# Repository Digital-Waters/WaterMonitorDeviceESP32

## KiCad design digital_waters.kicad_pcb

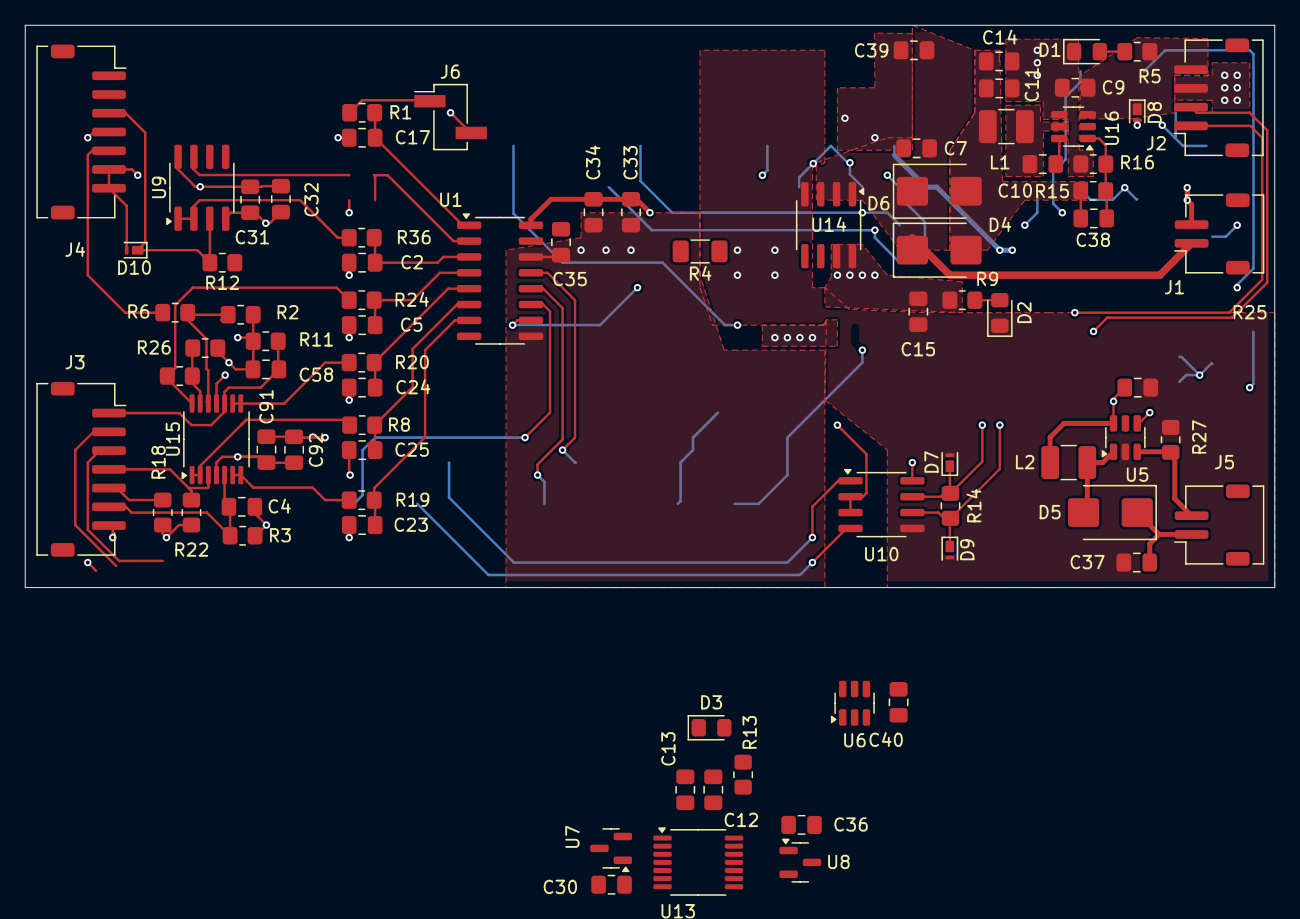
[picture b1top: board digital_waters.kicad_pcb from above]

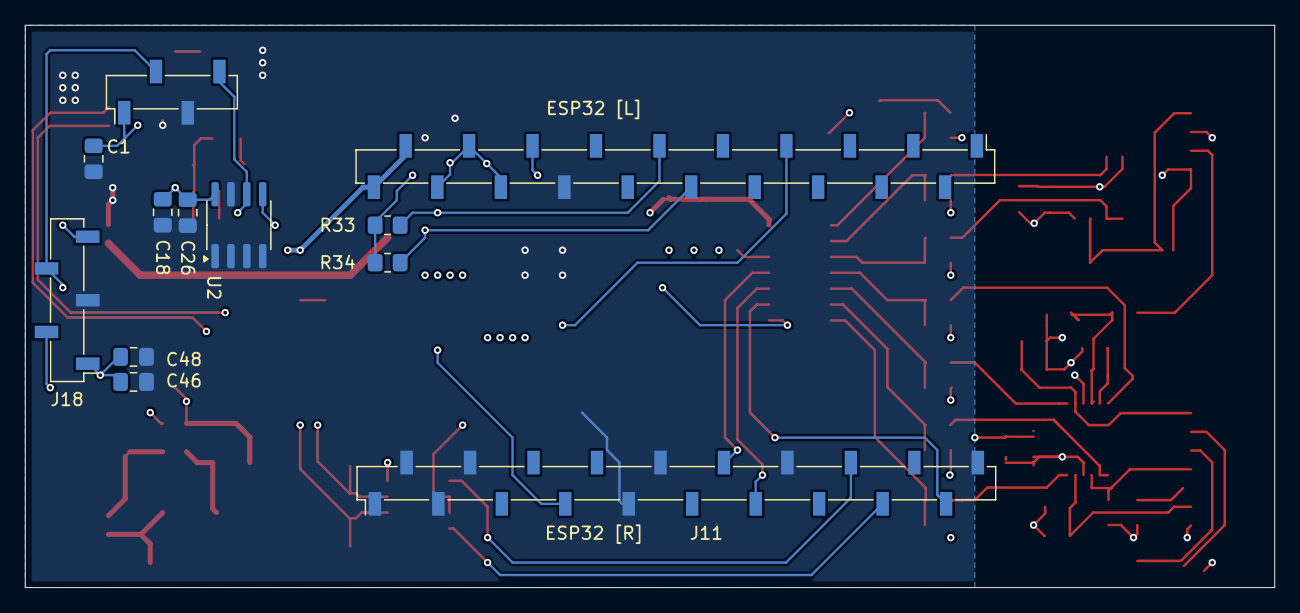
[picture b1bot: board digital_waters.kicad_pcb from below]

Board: 4 copper layers, 100.0 x 45.0 mm, 94 parts (12 on the bottom side), 55 nets.

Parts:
C1, C4, C10, C13, C26, C32, C46, C58, C92: 0.1u; C_0805_2012Metric_Pad1.18x1.45mm_HandSolder
C2, C5, C17, C23, C24, C25: 800n; C_0805_2012Metric_Pad1.18x1.45mm_HandSolder
C7, C9, C15, C29, C34: 10u; C_0805_2012Metric_Pad1.18x1.45mm_HandSolder
C11, C14: 22u; C_0805_2012Metric_Pad1.18x1.45mm_HandSolder
C12, C18, C31, C33, C35, C39, C40, C48, C91: 1u; C_0805_2012Metric_Pad1.18x1.45mm_HandSolder
C30, C36, C37: 0.47u; C_0805_2012Metric_Pad1.18x1.45mm_HandSolder
C38: 100p; C_0805_2012Metric_Pad1.18x1.45mm_HandSolder
D1: LED; LED_0805_2012Metric_Pad1.15x1.40mm_HandSolder
D2: 5V Global; LED_0805_2012Metric_Pad1.15x1.40mm_HandSolder
D3: 5V Switched; LED_0805_2012Metric_Pad1.15x1.40mm_HandSolder
D4, D5, D6: B230; D_SMB
D7, D9: PTVS10VZ1USK; Nexperia_DSN1608-2_1.6x0.8mm
D8: PTVS22VZ1USK; Nexperia_DSN1608-2_1.6x0.8mm
D10: PTVS5V0Z1USK; Nexperia_DSN1608-2_1.6x0.8mm
J1: Conn_Batt; JST_ZH_S2B-ZR-SM4A-TF_1x02-1MP_P1.50mm_Horizontal
J2: Conn_Remote; JST_ZH_S4B-ZR-SM4A-TF_1x04-1MP_P1.50mm_Horizontal
J3: Conn_Sense_A; JST_ZH_S7B-ZR-SM4A-TF_1x07-1MP_P1.50mm_Horizontal
J4: Conn_Sense_B; JST_ZH_S7B-ZR-SM4A-TF_1x07-1MP_P1.50mm_Horizontal
J5: Conn_Illum; JST_ZH_S2B-ZR-SM4A-TF_1x02-1MP_P1.50mm_Horizontal
J6: Cal_in; PinHeader_1x02_P2.54mm_Vertical_SMD_Pin1Left
J11: ESP32 [R]; PinSocket_1x20_P2.54mm_Vertical_SMD_Pin1Left
J16: ESP32 [L]; PinSocket_1x20_P2.54mm_Vertical_SMD_Pin1Left
J18: EZO Carrier Board; PinSocket_1x05_P2.54mm_Vertical_SMD_Pin1Left
L1: 3.3uH; L_1210_3225Metric_Pad1.42x2.65mm_HandSolder
L2: 22uH; L_1210_3225Metric_Pad1.42x2.65mm_HandSolder
R1, R8, R19, R20, R24, R36: 1k; R_0805_2012Metric_Pad1.20x1.40mm_HandSolder
R2, R3, R11: 100k; R_0805_2012Metric_Pad1.20x1.40mm_HandSolder
R4: 0 Ohm; R_1206_3216Metric_Pad1.30x1.75mm_HandSolder
R5: 2.2k; R_0805_2012Metric_Pad1.20x1.40mm_HandSolder
R6, R14: 100; R_0805_2012Metric_Pad1.20x1.40mm_HandSolder
R9, R13: 470; R_0805_2012Metric_Pad1.20x1.40mm_HandSolder
R12: 10k / 1%; R_0805_2012Metric_Pad1.20x1.40mm_HandSolder
R15: 62k / 1%; R_0805_2012Metric_Pad1.20x1.40mm_HandSolder
R16: 10k; R_0805_2012Metric_Pad1.20x1.40mm_HandSolder
R18: 470/1%; R_0805_2012Metric_Pad1.20x1.40mm_HandSolder
R22: 4.7k/1%; R_0805_2012Metric_Pad1.20x1.40mm_HandSolder
R25: 91k / 1%; R_0805_2012Metric_Pad1.20x1.40mm_HandSolder
R26: 100 / 1%; R_0805_2012Metric_Pad1.20x1.40mm_HandSolder
R27: 10 / 1%; R_0805_2012Metric_Pad1.20x1.40mm_HandSolder
R33, R34: 4.7k; R_0805_2012Metric_Pad1.20x1.40mm_HandSolder
U1: MCP3208; SOIC-16_3.9x9.9mm_P1.27mm
U2: M24C02-FMN; SOIC-8_3.9x4.9mm_P1.27mm
U5: DIO5661ST6; SOT-23-6
U6: TPS22929D; SOT-23-6
U7: REF3040; SOT-23
U8: REF3025; SOT-23
U9: TLV2387DR; SOIC-8_3.9x4.9mm_P1.27mm
U10: ST485E; SOIC-8_3.9x4.9mm_P1.27mm
U12: DHT20; PinSocket_1x04_P2.54mm_Vertical_SMD_Pin1Left
U13, U15: TLV4387; TSSOP-14_4.4x5mm_P0.65mm
U14: MCP1727-5002xSN; SOIC-8_3.9x4.9mm_P1.27mm
U16: AP63200WU; TSOT-23-6

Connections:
+3.3V: C1.1, C18.1, C26.1, C46.1, C48.1, J16.16, J16.17, J16.18, J18.1, R33.2, R34.2, U2.8 (VCC), U12.1 (VCC)
+5V: C15.1, C29.1, C40.1, J16.19, J16.20, L2.1, R9.1, U5.6 (VIN), U6.4 (VIN), U6.6 (VIN), U10.8 (VCC), U14.7 (Sense), U14.8 (Vout)
+VSW: C12.1, C13.1, C30.1, C31.1, C32.1, C33.1, C34.1, C36.1, C91.1, C92.1, R13.1, U1.16 (Vdd), U6.1 (VOUT), U7.1 (IN), U8.1 (IN), U9.8 (V+), U13.4 (V+), U15.4 (V+)
/ADC_VREF: C35.1, R12.1, U1.15 (Vref), U13.1, U13.2 (-)
/EN/~SH_0: J11.7, J18.2, U5.4 (EN), U6.3 (ON)
/I2C_SCL: J16.11, J18.5, R33.1, U2.6 (SCL), U12.4 (I2C_SCL)
/I2C_SDA: J16.10, J18.4, R34.1, U2.5 (SDA), U12.2 (I2C_SDA)
/INPUT_OUTPUT_RS485_A: D9.1 (K), J2.2, R14.1, U10.6 (A)
/INPUT_OUTPUT_RS485_B: D7.1 (K), J2.1, R14.2, U10.7 (B)
/Micocontroller/COM_DE/RE*: J16.7, U10.2 (~RE), U10.3 (DE)
/Micocontroller/OUTPUT_ILLUMINATOR+: C37.1, D5.1 (K), J5.1
/Micocontroller/OUTPUT_ILLUMINATOR-: J5.2, R27.1, U5.3 (FB)
/Micocontroller/RXD: J11.16, U10.1 (RO)
/Micocontroller/TXD: J11.17, U10.4 (DI)
/Power/+2.5V_REF_BUF_A: J3.7, U13.8, U13.9 (-)
/Power/+2.5V_REF_BUF_B: J3.2, U13.13 (-), U13.14
/Power/+4.096_REF_BUF_B: J3.3, U13.6 (-), U13.7
/Power/INPUT_12V+: C9.1, D8.1 (K), J2.4, R5.1, U16.3 (IN)
/Power/INPUT_VBATT_+: C7.2, C39.1, D4.1 (K), D6.1 (K), J1.1, U14.1 (Vin), U14.2 (Vin), U14.3 (~SHDN)
/Power/U16-SW: C10.2, L1.1, U16.5 (SW)
/SPI_CS0: J16.15, U1.10 (~CS/SHDN)
/SPI_MISO: J11.13, U1.12 (Dout)
/SPI_MOSI: J11.19, U1.11 (Din)
/SPI_SCLK: J11.12, U1.13 (CLK)
/Sensor Module Prototype/ADC_CAL: C17.1, R1.2, U1.1 (CH0)
/Sensor Module Prototype/ADC_DO: C5.1, R24.2, U1.4 (CH3)
/Sensor Module Prototype/ADC_ORP: C24.1, R20.2, U1.5 (CH4)
/Sensor Module Prototype/ADC_PH: C23.1, R19.2, U1.7 (CH6)
/Sensor Module Prototype/ADC_TEMP_NTC_10k: C2.1, R36.2, U1.3 (CH2)
/Sensor Module Prototype/ADC_TURB: C25.1, R8.2, U1.6 (CH5)
/Sensor Module Prototype/INPUT_DO: J4.5, R6.1
/Sensor Module Prototype/INPUT_NTC10K: D10.1 (K), J4.3, R12.2, U9.3 (+)
/Sensor Module Prototype/INPUT_ORP+: C58.1, J3.1, R11.2, U15.10 (+)
/Sensor Module Prototype/INPUT_TURB_SIG: J3.4, R22.2, U15.3 (+)
/Sensor Module Prototype/INPUT_TURB_V-: J3.5, R18.2
/Sensor Module Prototype/INPUT_pH+: C4.1, J3.6, R3.2, U15.5 (+)
GNDA: C2.2, C4.2, C5.2, C12.2, C13.2, C17.2, C23.2, C24.2, C25.2, C30.2, C31.2, C32.2, C33.2, C34.2, C35.2, C36.2, C58.2, C91.2, C92.2, D3.1 (K), D10.2 (A), J4.4, J4.6, J4.7, J6.2, R2.1, R3.1, R11.1, R18.1, R22.1, R26.1, U1.9 (DGND), U1.14 (AGND), U7.3 (GND), U8.3 (GND), U9.4 (V-), U13.11 (V-), U15.11 (V-)
GNDD: C1.2, C7.1, C9.2, C11.2, C14.2, C15.2, C18.2, C26.2, C29.2, C37.2, C39.2, C40.2, C46.2, C48.2, D1.1 (K), D2.1 (K), D7.2 (A), D8.2 (A), D9.2 (A), J1.2, J2.3, J11.1, J11.2, J11.3, J11.4, J11.9, J11.10, J11.14, J11.20, J16.14, J18.3, R16.2, R27.2, U2.1 (E0), U2.2 (E1), U2.3 (E2), U2.4 (VSS), U2.7 (~WC), U5.2 (GND), U6.2 (GND), U6.5 (GND), U10.5 (GND), U12.3 (GND), U14.4 (GND), U16.4 (GND)
unnamed: D1.2 (A), R5.2
unnamed: D2.2 (A), R9.2
unnamed: D3.2 (A), R13.2
unnamed: C11.1, C14.1, C38.1, D4.2 (A), D6.2 (A), L1.2, R15.2
unnamed: D5.2 (A), L2.2, U5.1 (LX)
unnamed: J6.1, R1.1
unnamed: R24.1, R25.2, U15.14
unnamed: R36.1, U9.1, U9.2 (-)
unnamed: U7.2 (OUT), U13.3 (+), U13.5 (+)
unnamed: U8.2 (OUT), U13.10 (+), U13.12 (+)
unnamed: R8.1, U15.1, U15.2 (-)
unnamed: R19.1, U15.6 (-), U15.7
unnamed: R20.1, U15.8, U15.9 (-)
unnamed: R2.2, R6.2, U15.12 (+)
unnamed: R25.1, R26.2, U15.13 (-)
unnamed: C10.1, U16.6 (BST)
unnamed: C38.2, R15.1, R16.1, U16.1 (FB)

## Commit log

2025-07-25 Inception Moving this project from atop8918's repo to the Digital Waters' repo
2025-09-15 Prototype v0.3.1 WIP Just a maintenance checkin. Many changes - Removed the Base Sensor schematic and put all sensors into SensorPrototype - Added a constant current LED driver for camera illuminatio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
2025-09-22 Board V0.0.3 Everything is routed and connected ERC and DRC run without serious error. (There are DRC violations due to a VSSP-83x3mm package but I'm not sure why)
2025-09-23 BUG FIX -------- There were some issues with the board WRT manufacturing. I changed the VSSOP 8 packages to SOT versions and re-routed
2025-11-18 Maintenance update - Adding the EC isolation board schematic - Added a harness page for wireing module together
2026-05-04 feature/v3.1/setup - Inception - some general changes in support of v3.1 before I thought to branch.
